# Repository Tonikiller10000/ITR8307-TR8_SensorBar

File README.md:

# ITR8307-TR8_SensorBar
## An 8 sensor sensor bar using ITR8307-TR8 SMD sensors.
The sensor bar was made with the ITR8307-TR8 smd sensors on only one PCB layer and was meant to be used in the Linefollower project to detect a black line on the white surface. 

### How it works:

<table>
  <tr>
    <td></td heigth=300>
    <td> The ITR8307 sensor contain an IR led witch send`s infrared ligth to an object and it`s recived back by an IR photoresistor with witch it can calculate the distance between the surface and the sensor.</td>
  </tr>
 </table>

With an 220R resistor to the internal IR LED and an 10K resistor to the photroresistor to create an voltage devider, the sensor return values from 0 to 5v in function of the distance between the sensor and the object. 

Schematic:

Links:
- ITR8307-TR8: https://pdf1.alldatasheet.com/datasheet-pdf/view/105612/EVERLIGHT/ITR8307.html
- Code for testing: https://github.com/Tonikiller10000/ITR8307-TR8_SensorBar/tree/main/SensorBarTesting
- Assenmbly: https://github.com/Tonikiller10000/ITR8307-TR8_SensorBar/blob/main/SensorBar_Pictures/assembly1.jpg
- QRE1113GR(sensor alternative): https://www.pololu.com/file/0J117/QRE1113GR.pdf
- Bar 3D view schematic: https://www.pololu.com/file/0J1288/qtr-8x-reflectance-sensor-array-dimensions.pdf 
- Polulu sensor bar buy: https://www.pololu.com/product/960
- Pololu - QTR-8A and QTR-8RC Reflectance Sensor Array User's Guide: https://www.pololu.com/docs/pdf/0J12/QTR-8x.pdf

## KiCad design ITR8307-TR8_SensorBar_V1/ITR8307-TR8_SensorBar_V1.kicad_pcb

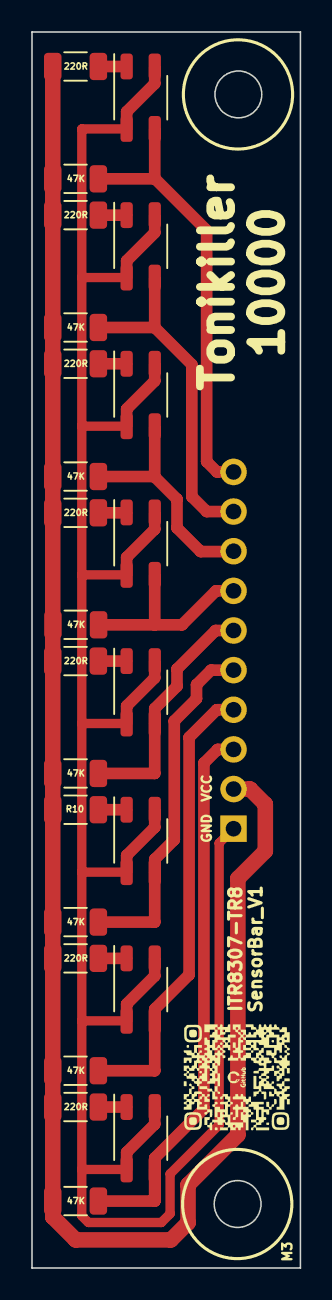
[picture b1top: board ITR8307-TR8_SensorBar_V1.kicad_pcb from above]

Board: 2 copper layers, 17.2 x 79.2 mm, 25 parts (1 on the bottom side), 18 nets.

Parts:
J1: Conn_01x10_Pin; PinHeader_1x10_P2.54mm_Horizontal
R1, R2, R5, R6, R9, R10, R13, R14: 220R; R_1206_3216Metric
R3, R4, R7, R8, R11, R12, R15, R16: 47K; R_1206_3216Metric
U1, U2, U3, U4, U5, U6, U7, U8: ITR8307; Everlight_ITR1201SR10AR

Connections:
+5V: J1.2, R1.1, R2.1, R3.1, R4.1, R5.1, R6.1, R7.1, R8.1, R9.1, R10.1, R11.1, R12.1, R13.1, R14.1, R15.1, R16.1
A0: J1.3, R4.2, U2.3 (C)
A1: J1.4, R8.2, U4.3 (C)
A2: J1.5, R12.2, U6.3 (C)
A3: J1.6, R16.2, U8.3 (C)
A4: J1.7, R3.2, U1.3 (C)
A5: J1.8, R7.2, U3.3 (C)
A6: J1.9, R11.2, U5.3 (C)
A7: J1.10, R15.2, U7.3 (C)
GND: J1.1, U1.1 (K), U1.4 (E), U2.1 (K), U2.4 (E), U3.1 (K), U3.4 (E), U4.1 (K), U4.4 (E), U5.1 (K), U5.4 (E), U6.1 (K), U6.4 (E), U7.1 (K), U7.4 (E), U8.1 (K), U8.4 (E)
unnamed: R1.2, U1.2 (A)
unnamed: R2.2, U2.2 (A)
unnamed: R5.2, U3.2 (A)
unnamed: R6.2, U4.2 (A)
unnamed: R9.2, U5.2 (A)
unnamed: R10.2, U6.2 (A)
unnamed: R13.2, U7.2 (A)
unnamed: R14.2, U8.2 (A)
